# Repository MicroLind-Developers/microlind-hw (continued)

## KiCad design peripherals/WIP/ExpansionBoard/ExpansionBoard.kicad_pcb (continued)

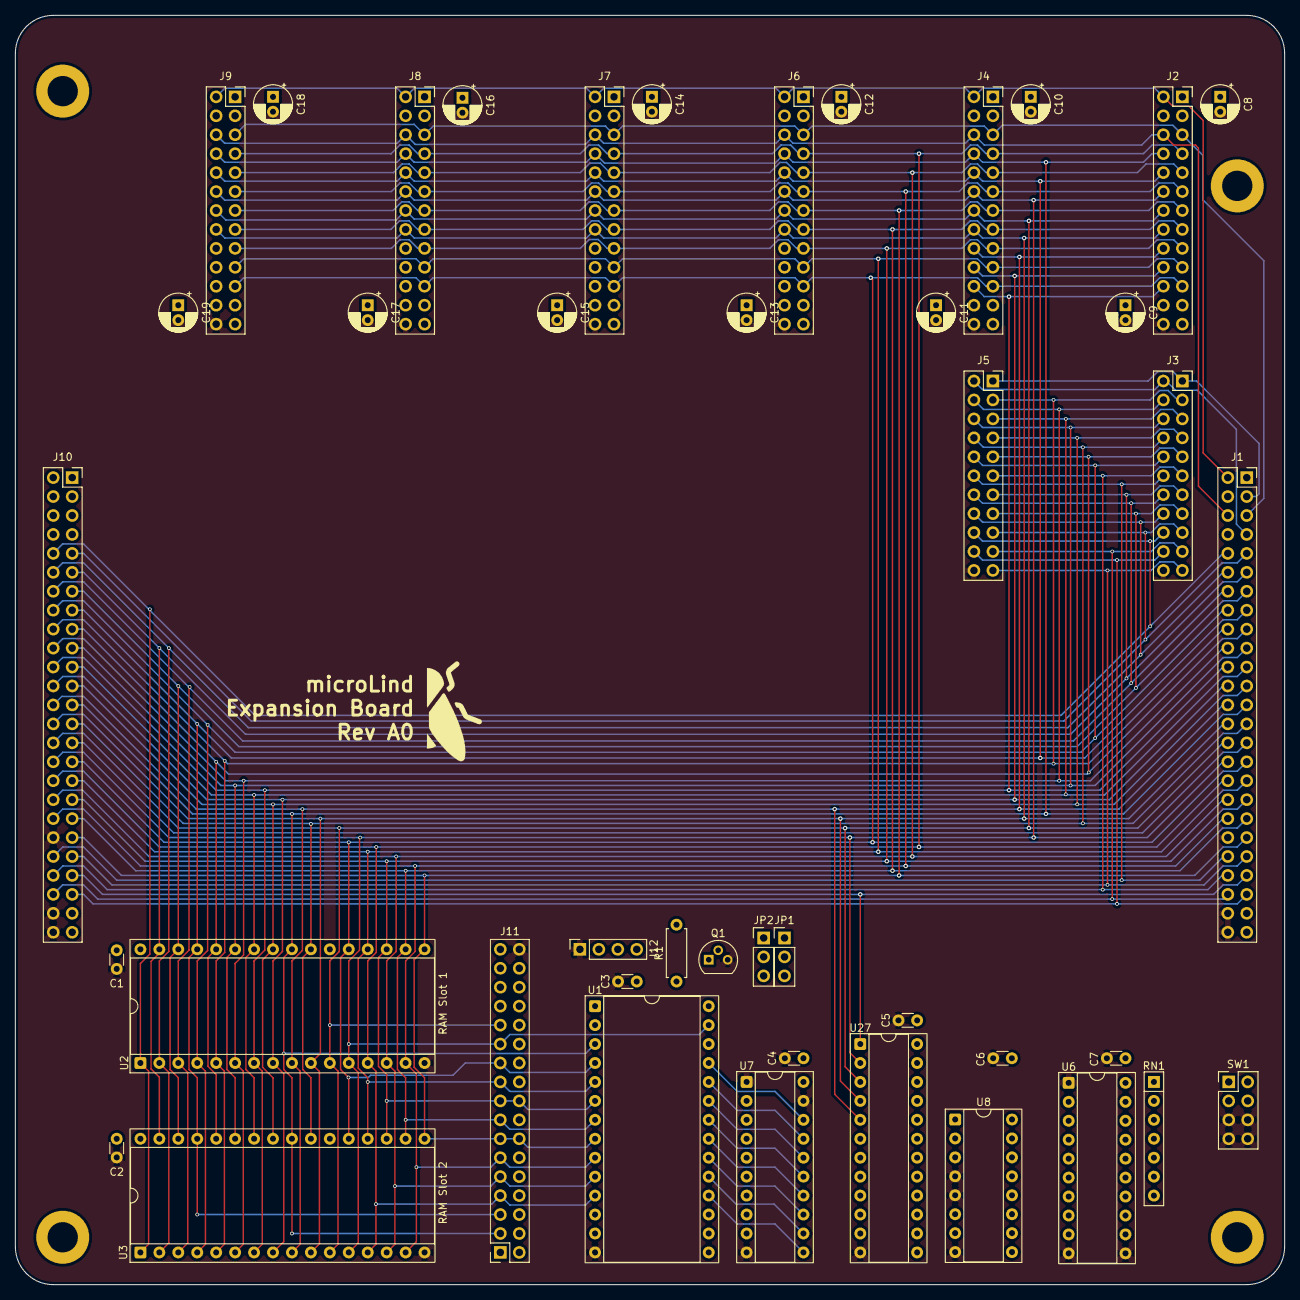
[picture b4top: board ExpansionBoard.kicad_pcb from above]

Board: 4 copper layers, 170.2 x 170.2 mm, 45 parts (0 on the bottom side), 94 nets.

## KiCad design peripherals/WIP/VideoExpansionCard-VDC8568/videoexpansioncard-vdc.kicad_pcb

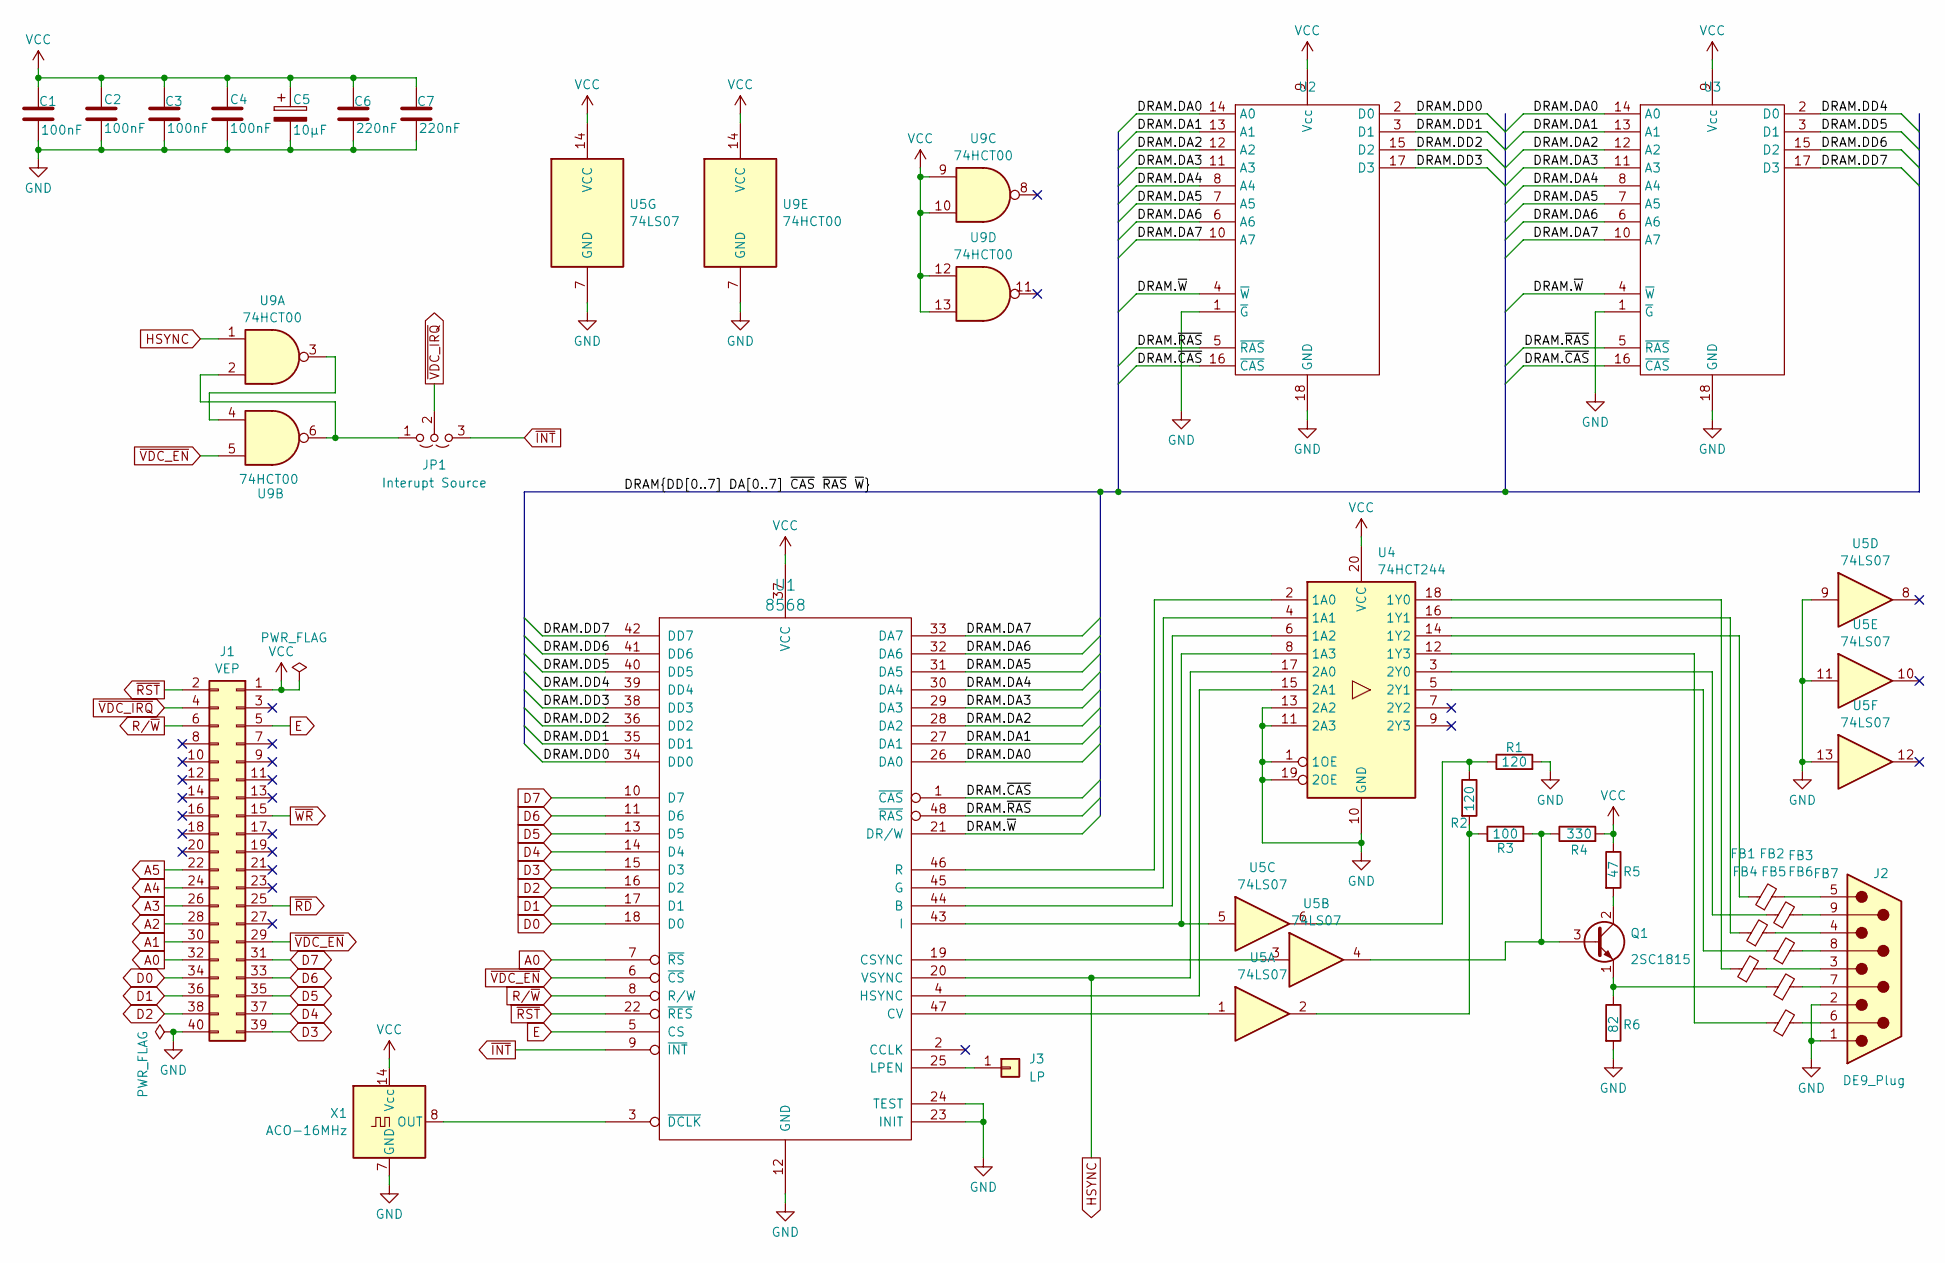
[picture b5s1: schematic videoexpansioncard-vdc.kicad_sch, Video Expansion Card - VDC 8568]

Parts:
C1, C2, C3, C4: 100nF; C_Disc_D5.0mm_W2.5mm_P2.50mm
C5: 10µF; CP_Radial_D5.0mm_P2.00mm
C6, C7: 220nF; C_Disc_D5.0mm_W2.5mm_P2.50mm
FB1, FB2, FB3, FB4, FB5, FB6, FB7: FerriteBead_Small; L_Axial_L5.0mm_D3.6mm_P10.00mm_Horizontal_Murata_BL01RN1A2A2
J1: VEP; GraphicsCardTemplate
J2: DE9_Plug; DSUB-9_Male_Horizontal_P2.77x2.54mm_EdgePinOffset9.40mm
J3: LP; PinHeader_1x01_P2.54mm_Vertical
JP1: Interupt Source; PinHeader_1x03_P2.54mm_Vertical
Q1: 2SC1815; TO-92_Inline
R1, R2: 120; R_Axial_DIN0207_L6.3mm_D2.5mm_P10.16mm_Horizontal
R3: 100; R_Axial_DIN0207_L6.3mm_D2.5mm_P10.16mm_Horizontal
R4: 330; R_Axial_DIN0207_L6.3mm_D2.5mm_P10.16mm_Horizontal
R5: 47; R_Axial_DIN0207_L6.3mm_D2.5mm_P10.16mm_Horizontal
R6: 82; R_Axial_DIN0207_L6.3mm_D2.5mm_P10.16mm_Horizontal
U1: 8568; DIP-48_W15.24mm_Socket
U2, U3: DIP-18_W7.62mm_Socket
U4: 74HCT244; DIP-20_W7.62mm_Socket
U5: 74LS07; DIP-14_W7.62mm_Socket
U9: 74HCT00; DIP-14_W7.62mm_Socket
X1: ACO-16MHz; Oscillator_DIP-14

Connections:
/DRAM.DA0: U1.26 (DA0), U2.14 (A0), U3.14 (A0)
/DRAM.DA1: U1.27 (DA1), U2.13 (A1), U3.13 (A1)
/DRAM.DA2: U1.28 (DA2), U2.12 (A2), U3.12 (A2)
/DRAM.DA3: U1.29 (DA3), U2.11 (A3), U3.11 (A3)
/DRAM.DA4: U1.30 (DA4), U2.8 (A4), U3.8 (A4)
/DRAM.DA5: U1.31 (DA5), U2.7 (A5), U3.7 (A5)
/DRAM.DA6: U1.32 (DA6), U2.6 (A6), U3.6 (A6)
/DRAM.DA7: U1.33 (DA7), U2.10 (A7), U3.10 (A7)
/DRAM.DD0: U1.34 (DD0), U2.2 (D0)
/DRAM.DD1: U1.35 (DD1), U2.3 (D1)
/DRAM.DD2: U1.36 (DD2), U2.15 (D2)
/DRAM.DD3: U1.38 (DD3), U2.17 (D3)
/DRAM.DD4: U1.39 (DD4), U3.2 (D0)
/DRAM.DD5: U1.40 (DD5), U3.3 (D1)
/DRAM.DD6: U1.41 (DD6), U3.15 (D2)
/DRAM.DD7: U1.42 (DD7), U3.17 (D3)
/DRAM.~CAS: U1.1 (~CAS), U2.16 (~CAS), U3.16 (~CAS)
/DRAM.~RAS: U1.48 (~RAS), U2.5 (~RAS), U3.5 (~RAS)
/DRAM.~W: U1.21 (DR/W), U2.4 (~W), U3.4 (~W)
A0: J1.32, U1.7 (~RS)
A1: J1.30
A2: J1.28
A3: J1.26
A4: J1.24
A5: J1.22
D0: J1.34, U1.18 (D0)
D1: J1.36, U1.17 (D1)
D2: J1.38, U1.16 (D2)
D3: J1.39, U1.15 (D3)
D4: J1.37, U1.14 (D4)
D5: J1.35, U1.13 (D5)
D6: J1.33, U1.11 (D6)
D7: J1.31, U1.10 (D7)
E: J1.5, U1.5 (CS)
GND: C1.2, C2.2, C3.2, C4.2, C5.2, C6.2, C7.2, J1.40, J2.1, J2.2, R1.2, R6.2, U1.12 (GND), U1.23 (INIT), U1.24 (TEST), U2.1 (~G), U2.18 (GND), U3.1 (~G), U3.18 (GND), U4.1 (1OE), U4.10 (GND), U4.11 (2A3), U4.13 (2A2), U4.19 (2OE), U5.7 (GND), U5.9, U5.11, U5.13, U9.7 (GND), X1.7 (GND)
HSYNC: U1.20 (VSYNC), U4.17 (2A0), U9.1
unnamed: FB1.2, J2.5
unnamed: FB2.2, J2.9
unnamed: FB3.2, J2.4
unnamed: FB4.2, J2.8
unnamed: FB5.2, J2.3
unnamed: FB6.2, J2.7
unnamed: FB7.2, J2.6
unnamed: J3.1 (Pin_1_1), U1.25 (LPEN)
unnamed: JP1.1 (A), U9.2, U9.6
unnamed: Q1.3 (B), R3.2, R4.1, U5.4
unnamed: Q1.2 (C), R5.2
unnamed: FB6.1, Q1.1 (E), R6.1
unnamed: R1.1, R2.1, U5.6
unnamed: R2.2, R3.1, U5.2
unnamed: U1.44 (B), U4.6 (1A2)
unnamed: U1.19 (CSYNC), U5.3
unnamed: U1.47 (CV), U5.1
unnamed: U1.45 (G), U4.4 (1A1)
unnamed: U1.4 (HSYNC), U4.15 (2A1)
unnamed: U1.43 (I), U4.8 (1A3), U5.5
unnamed: U1.46 (R), U4.2 (1A0)
unnamed: U1.3 (~DCLK), X1.8 (OUT)
unnamed: FB5.1, U4.18 (1Y0)
unnamed: FB3.1, U4.16 (1Y1)
unnamed: FB1.1, U4.14 (1Y2)
unnamed: FB7.1, U4.12 (1Y3)
unnamed: FB2.1, U4.3 (2Y0)
unnamed: FB4.1, U4.5 (2Y1)
unnamed: U9.3, U9.4
R/~W: J1.6, U1.8 (R/W)
VCC: C1.1, C2.1, C3.1, C4.1, C5.1, C6.1, C7.1, J1.1, R4.2, R5.1, U1.37 (VCC), U2.9 (Vcc), U3.9 (Vcc), U4.20 (VCC), U5.14 (VCC), U9.9, U9.10, U9.12, U9.13, U9.14 (VCC), X1.14 (Vcc)
~INT: JP1.3 (B), U1.9 (~INT)
~RD: J1.25
~RST: J1.2, U1.22 (~RES)
~VDC_EN: J1.29, U1.6 (~CS), U9.5
~VDC_IRQ: J1.4, JP1.2 (C)
~WR: J1.15

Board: 2 copper layers, 32 parts (0 on the bottom side), 66 nets, no tracks yet.

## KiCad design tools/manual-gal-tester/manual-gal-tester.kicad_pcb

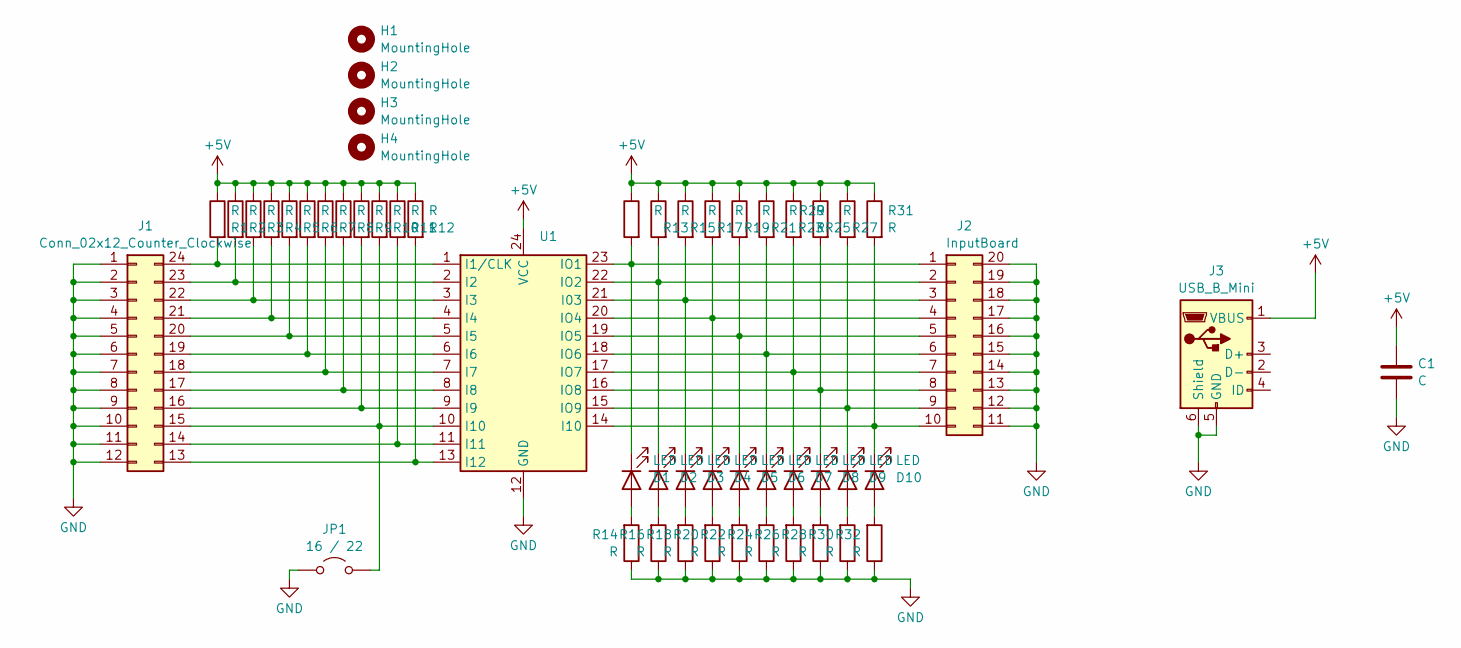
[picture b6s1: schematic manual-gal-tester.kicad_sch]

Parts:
C1: C; C_Radial_D5.0mm_H5.0mm_P2.00mm
D1, D2, D3, D4, D5, D6, D7, D8, D9, D10: LED; LED_D5.0mm
H1, H2, H3, H4: MountingHole; MountingHole_3.2mm_M3
J1: Conn_02x12_Counter_Clockwise; DIP-24_W7.62mm_Socket
J2: InputBoard; DIP-20_W7.62mm_Socket
J3: USB_B_Mini; USB_B_Lumberg_2411_02_Horizontal
JP1: 16 / 22; PinHeader_1x02_P2.54mm_Vertical
R1, R2, R3, R4, R5, R6, R7, R8, R9, R10, R11, R12, R13, R14, R15, R16, R17, R18, R19, R20, R21, R22, R23, R24, R25, R26, R27, R28, R29, R30, R31, R32: R; R_Axial_DIN0207_L6.3mm_D2.5mm_P2.54mm_Vertical
U1: DIP_Socket-24_W4.3_W5.08_W7.62_W10.16_W10.9_3M_224-5248-00-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

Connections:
+5V: C1.1, J3.1 (VBUS), R1.1, R2.1, R3.1, R4.1, R5.1, R6.1, R7.1, R8.1, R9.1, R10.1, R11.1, R12.1, R13.1, R15.1, R17.1, R19.1, R21.1, R23.1, R25.1, R27.1, R29.1, R31.1, U1.24 (VCC)
GND: C1.2, J1.1, J1.2, J1.3, J1.4, J1.5, J1.6, J1.7, J1.8, J1.9, J1.10, J1.11, J1.12, J2.11, J2.12, J2.13, J2.14, J2.15, J2.16, J2.17, J2.18, J2.19, J2.20, J3.5 (GND), J3.6 (Shield), JP1.1 (A), R14.1, R16.1, R18.1, R20.1, R22.1, R24.1, R26.1, R28.1, R30.1, R32.1, U1.12 (GND)
unnamed: D1.2 (A), R14.2
unnamed: D1.1 (K), J2.1, R13.2, U1.23 (IO1)
unnamed: D2.2 (A), R16.2
unnamed: D2.1 (K), J2.2, R15.2, U1.22 (IO2)
unnamed: D3.2 (A), R18.2
unnamed: D3.1 (K), J2.3, R17.2, U1.21 (I03)
unnamed: D4.2 (A), R20.2
unnamed: D4.1 (K), J2.4, R19.2, U1.20 (IO4)
unnamed: D5.2 (A), R22.2
unnamed: D5.1 (K), J2.5, R21.2, U1.19 (IO5)
unnamed: D6.2 (A), R24.2
unnamed: D6.1 (K), J2.6, R23.2, U1.18 (IO6)
unnamed: D7.2 (A), R26.2
unnamed: D7.1 (K), J2.7, R25.2, U1.17 (IO7)
unnamed: D8.2 (A), R28.2
unnamed: D8.1 (K), J2.8, R27.2, U1.16 (IO8)
unnamed: D9.2 (A), R30.2
unnamed: D9.1 (K), J2.9, R29.2, U1.15 (IO9)
unnamed: D10.2 (A), R32.2
unnamed: D10.1 (K), J2.10, R31.2, U1.14 (I10)
unnamed: J1.13, R12.2, U1.13 (I12)
unnamed: J1.14, R11.2, U1.11 (I11)
unnamed: J1.15, JP1.2 (B), R10.2, U1.10 (I10)
unnamed: J1.16, R9.2, U1.9 (I9)
unnamed: J1.17, R8.2, U1.8 (I8)
unnamed: J1.18, R7.2, U1.7 (I7)
unnamed: J1.19, R6.2, U1.6 (I6)
unnamed: J1.20, R5.2, U1.5 (I5)
unnamed: J1.21, R4.2, U1.4 (I4)
unnamed: J1.22, R3.2, U1.3 (I3)
unnamed: J1.23, R2.2, U1.2 (I2)
unnamed: J1.24, R1.2, U1.1 (I1/CLK)

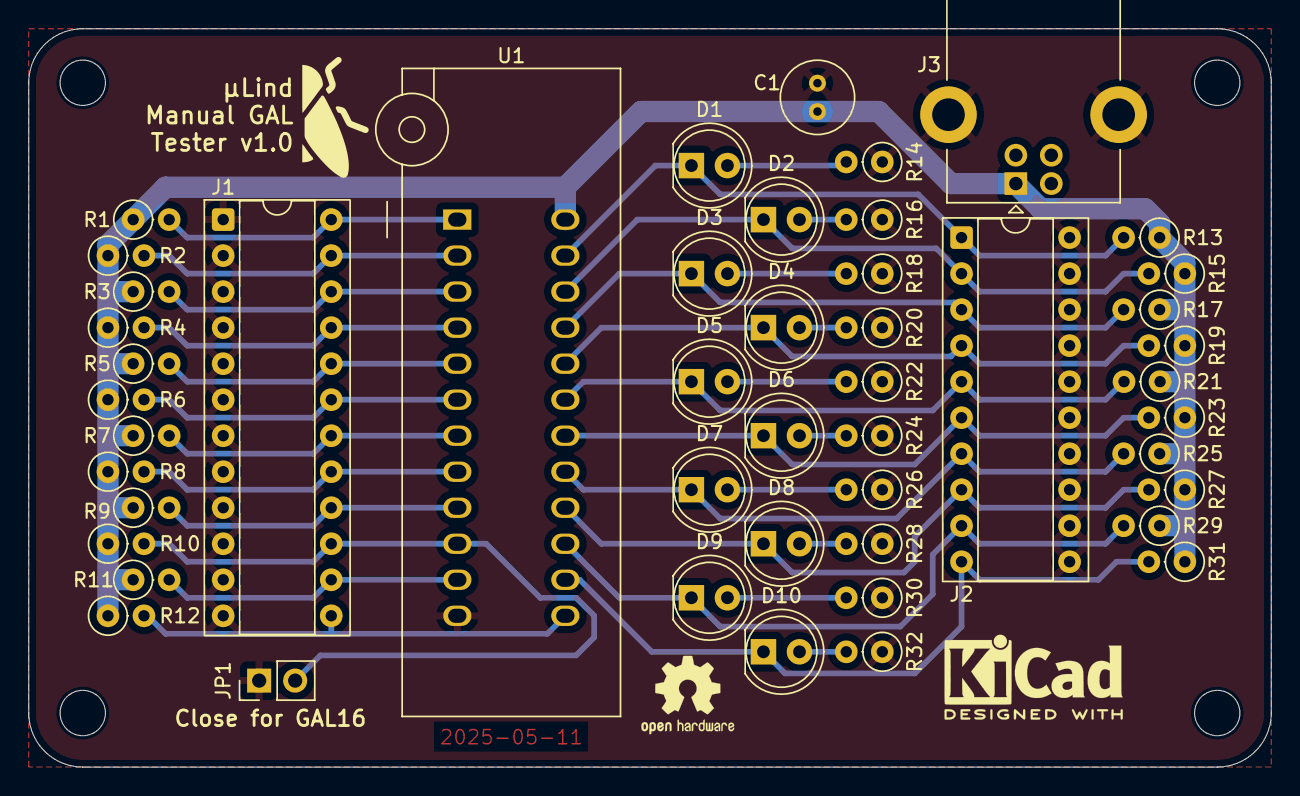
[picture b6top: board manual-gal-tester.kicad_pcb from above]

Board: 2 copper layers, 87.6 x 52.1 mm, 52 parts (0 on the bottom side), 34 nets.

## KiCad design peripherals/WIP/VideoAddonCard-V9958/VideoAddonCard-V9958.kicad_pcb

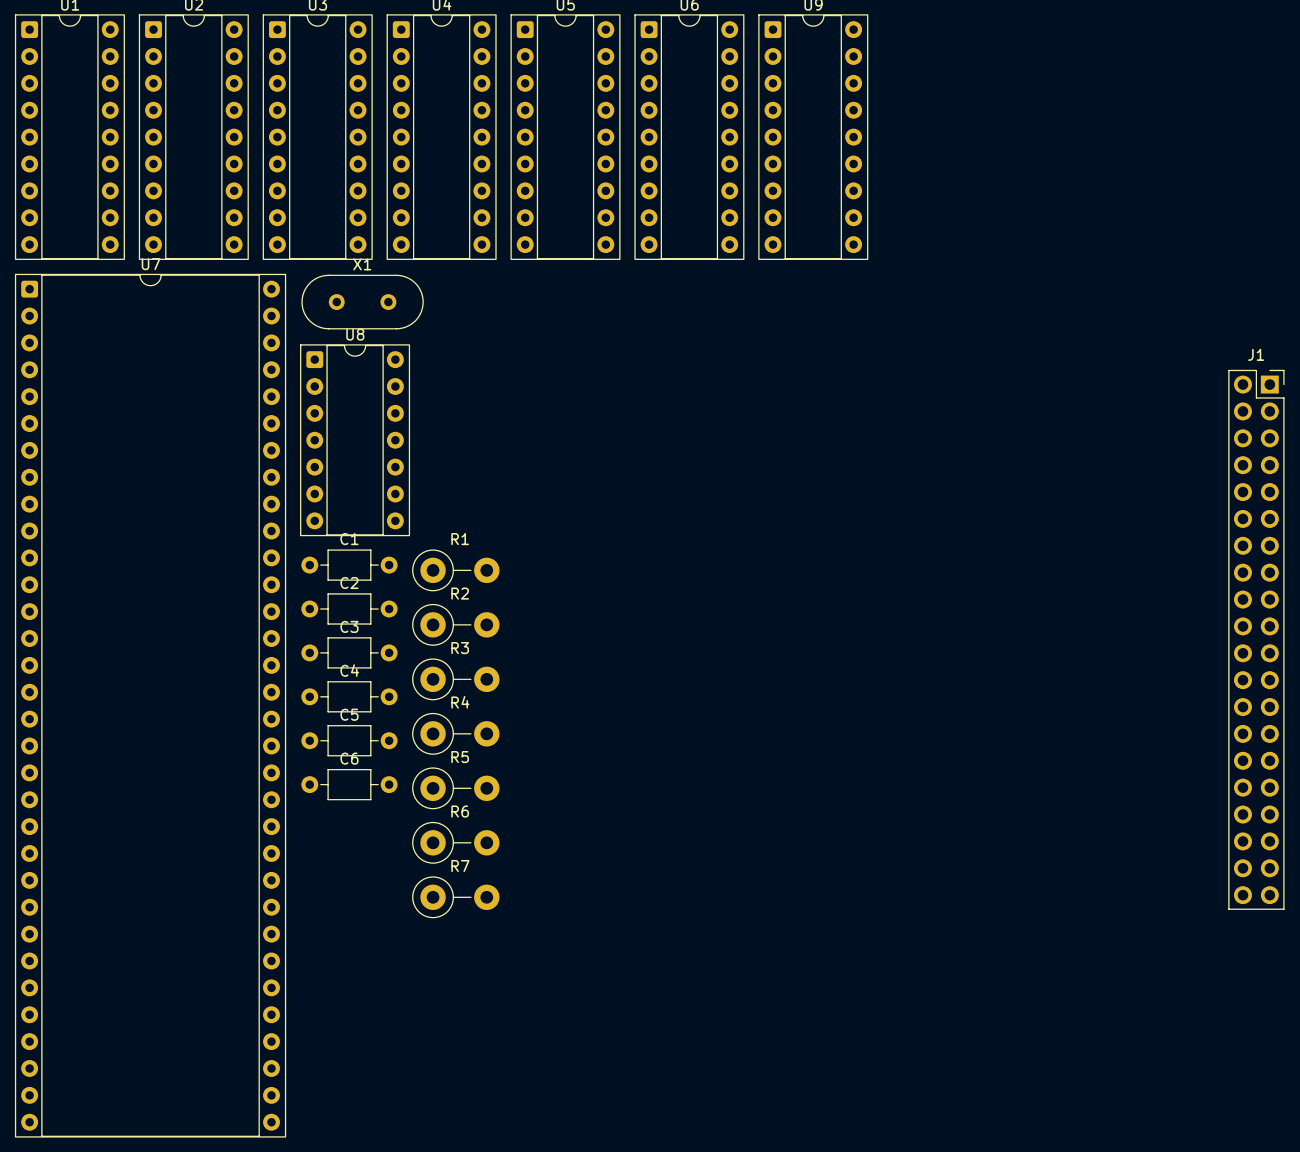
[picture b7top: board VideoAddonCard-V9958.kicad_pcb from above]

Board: 2 copper layers, 24 parts (0 on the bottom side), 53 nets, no tracks yet.

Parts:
C1, C2: C; C_Axial_L3.8mm_D2.6mm_P7.50mm_Horizontal
C3, C4, C5: 100nF; C_Axial_L3.8mm_D2.6mm_P7.50mm_Horizontal
C6: 47pF; C_Axial_L3.8mm_D2.6mm_P7.50mm_Horizontal
J1: VideoAddon; PinSocket_2x20_P2.54mm_Vertical
R1, R2, R3: 470; R_Axial_DIN0411_L9.9mm_D3.6mm_P5.08mm_Vertical
R4: 2k61; R_Axial_DIN0411_L9.9mm_D3.6mm_P5.08mm_Vertical
R5, R6: 4k7; R_Axial_DIN0411_L9.9mm_D3.6mm_P5.08mm_Vertical
R7: 2k2; R_Axial_DIN0411_L9.9mm_D3.6mm_P5.08mm_Vertical
U1, U2, U3, U4, U5, U6: 41464; DIP-18_W7.62mm_Socket
U7: V9958; DIP-64_W22.86mm_Socket
U8: 74LS32; DIP-14_W7.62mm_Socket
U9: DIP-18_W7.62mm_Socket
X1: Crystal_Generic; Crystal_HC49-4H_Vertical

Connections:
/A0: J1.32, U7.29 (A0)
/A1: J1.30, U7.28 (A1)
B_OUT: C5.1, R3.1, U7.24 (BLUE)
D0: J1.34, U7.40 (D0)
D1: J1.36, U7.39 (D1)
D2: J1.38, U7.38 (D2)
D3: J1.39, U7.37 (D3)
D4: J1.37, U7.36 (D4)
D5: J1.35, U7.35 (D5)
D6: J1.33, U7.34 (D6)
D7: J1.31, U7.32 (D7)
GND: C1.1, C2.1, C6.1, J1.40, R1.2, R2.2, R3.2, U1.18 (GND), U2.18 (GND), U3.18 (GND), U4.18 (GND), U5.18 (GND), U6.18 (GND), U7.1 (GND), U7.20 (GND/DAC), U8.9, U8.10, U8.12, U8.13, U9.1 (GND), U9.7 (N_PIN)
G_OUT: C4.1, R1.1, U7.23 (RED)
unnamed: C3.2, U9.2 (B_IN)
unnamed: C5.2, U9.4 (B_IN)
unnamed: C1.2, U7.63 (XTAL1), X1.1
unnamed: C2.2, U7.64 (XTAL2), X1.2
unnamed: U7.31 (~CSR), U8.6
unnamed: U7.30 (~CSW), U8.3
unnamed: R5.1, U7.27 (~H_RESET)
unnamed: R6.1, U7.4 (~V_RESET)
unnamed: C4.2, U9.3 (G_IN)
unnamed: C6.2, R7.2, U9.10 (SYNC_IN)
unnamed: R4.2, U9.17 (Y_TRAP)
R_OUT: C3.1, R2.1, U7.22 (GREEN)
VA0: U1.14 (A0), U2.14 (A0), U3.14 (A0), U4.14 (A0), U5.14 (A0), U6.14 (A0), U7.49 (VA0)
VA1: U1.13 (A1), U2.13 (A1), U3.13 (A1), U4.13 (A1), U5.13 (A1), U6.13 (A1), U7.50 (VA1)
VA2: U1.12 (A2), U2.12 (A2), U3.12 (A2), U4.12 (A2), U5.12 (A2), U6.12 (A2), U7.51 (VA2)
VA3: U1.11 (A3), U2.11 (A3), U3.11 (A3), U4.11 (A3), U5.11 (A3), U6.11 (A3), U7.52 (VA3)
VA4: U1.8 (A4), U2.8 (A4), U3.8 (A4), U4.8 (A4), U5.8 (A4), U6.8 (A4), U7.53 (VA4)
VA5: U1.7 (A5), U2.7 (A5), U3.7 (A5), U4.7 (A5), U5.7 (A5), U6.7 (A5), U7.54 (VA5)
VA6: U1.6 (A6), U2.6 (A6), U3.6 (A6), U4.6 (A6), U5.6 (A6), U6.6 (A6), U7.55 (VA6)
VA7: U1.10 (A7), U2.10 (A7), U3.10 (A7), U4.10 (A7), U5.10 (A7), U6.10 (A7), U7.56 (VA7)
VCC: J1.1, R4.1, R5.2, R6.2, U1.9 (VCC), U2.9 (VCC), U3.9 (VCC), U4.9 (VCC), U5.9 (VCC), U6.9 (VCC), U7.21 (VCC/DAC), U7.58 (VCC), U9.12 (VCC)
VD0: U1.2 (D0), U3.2 (D0), U5.2 (D0), U7.41 (VD0)
VD1: U1.3 (D1), U3.3 (D1), U5.3 (D1), U7.42 (VD1)
VD2: U1.15 (D2), U3.15 (D2), U5.15 (D2), U7.43 (VD2)
VD3: U1.17 (D3), U3.17 (D3), U5.17 (D3), U7.44 (VD3)
VD4: U2.2 (D0), U4.2 (D0), U6.2 (D0), U7.45 (VD4)
VD5: U2.3 (D1), U4.3 (D1), U6.3 (D1), U7.46 (VD5)
VD6: U2.15 (D2), U4.15 (D2), U6.15 (D2), U7.47 (VD6)
VD7: U2.17 (D3), U4.17 (D3), U6.17 (D3), U7.48 (VD7)
_CAS0: U1.16 (~CAS), U2.16 (~CAS), U7.61 (~CAS0)
_CAS1: U3.16 (~CAS), U4.16 (~CAS), U7.60 (~CAS1)
_CAS2: U5.16 (~CAS), U6.16 (~CAS), U7.59 (~CASX)
_R: U1.1 (~OE), U2.1 (~OE), U3.1 (~OE), U4.1 (~OE), U5.1 (~OE), U6.1 (~OE)
_RAS: U1.5 (~RAS), U2.5 (~RAS), U3.5 (~RAS), U4.5 (~RAS), U5.5 (~RAS), U6.5 (~RAS), U7.62 (~RAS)
_W: U1.4 (~W), U2.4 (~W), U3.4 (~W), U4.4 (~W), U5.4 (~W), U6.4 (~W)
~IRQ: J1.4, U7.25 (~INT)
~RD: J1.25, U8.5
~RST: J1.2, U7.9 (~RESET)
~VDC_EN: J1.29, U8.1, U8.4
~WR: J1.15, U8.2

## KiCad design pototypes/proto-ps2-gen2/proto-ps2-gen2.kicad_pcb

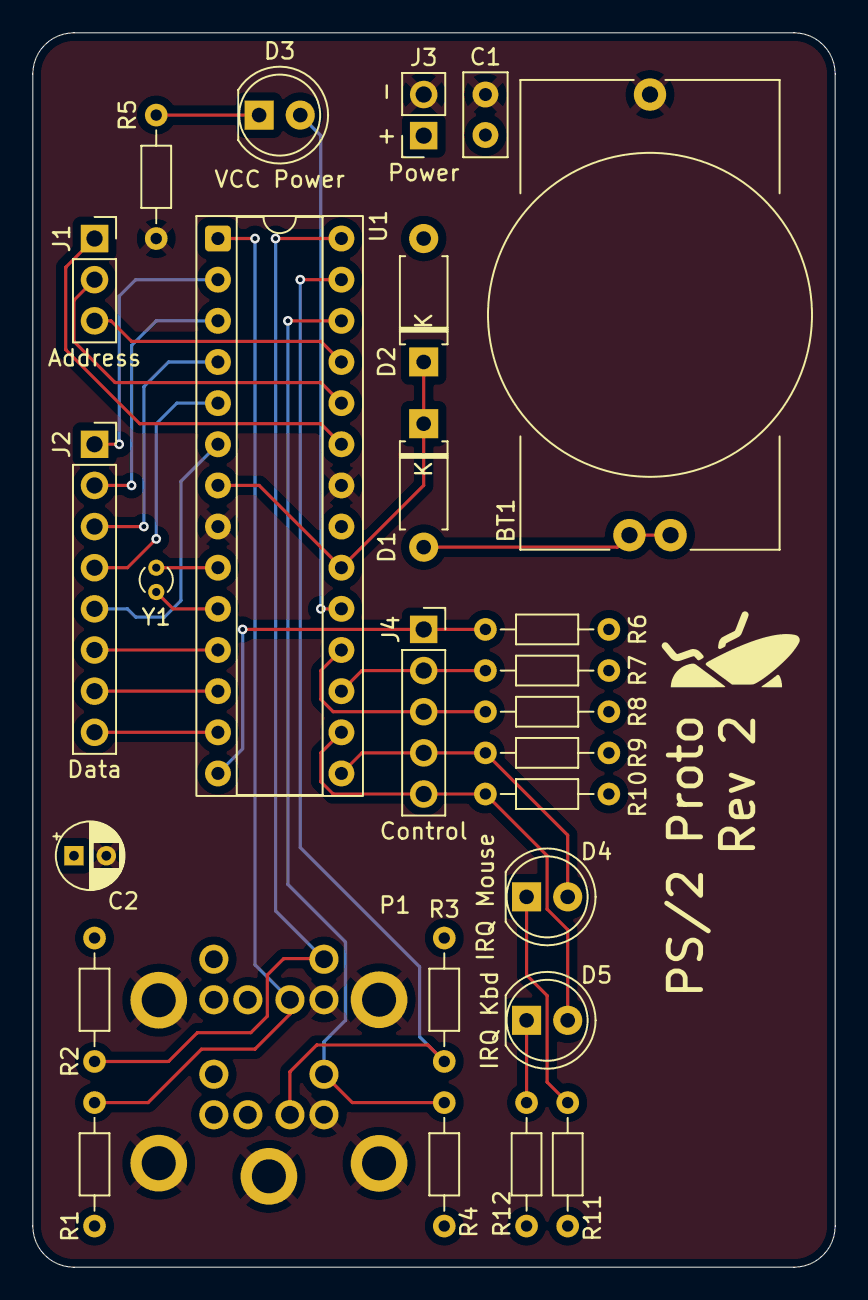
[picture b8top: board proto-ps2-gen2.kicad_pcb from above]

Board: 2 copper layers, 49.5 x 76.2 mm, 27 parts (0 on the bottom side), 30 nets.

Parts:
BT1: 2032; HU2032-CoinCellHolder
C1: 100n; C_Disc_D5.0mm_W2.5mm_P2.50mm
C2: 10u; CP_Radial_D4.0mm_P2.00mm
D1, D2: BAT41; D_A-405_P7.62mm_Horizontal
D3: VCC Power; LED_D5.0mm
D4: IRQ Mouse; LED_D5.0mm
D5: IRQ Kbd; LED_D5.0mm
J1: Address; PinSocket_1x03_P2.54mm_Vertical
J2: Data; PinSocket_1x08_P2.54mm_Vertical
J3: Power; PinSocket_1x02_P2.54mm_Vertical
J4: Control; PinSocket_1x05_P2.54mm_Vertical
P1: 2xPS2-Mini-Din
R1, R2, R3, R4, R6, R7, R8, R9, R10: 10k; R_Axial_DIN0204_L3.6mm_D1.6mm_P7.62mm_Horizontal
R5, R11, R12: 470; R_Axial_DIN0204_L3.6mm_D1.6mm_P7.62mm_Horizontal
U1: ATmega88; DIP-28_W7.62mm_Socket
Y1: 32.768kHz; Crystal_DS10_D1.0mm_L4.3mm_Vertical

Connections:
/A0: J1.1, U1.23 (PC0)
/A1: J1.2, U1.24 (PC1)
/A2: J1.3, U1.25 (PC2)
/D0: J2.1, U1.2 (PD0)
/D1: J2.2, U1.3 (PD1)
/D2: J2.3, U1.4 (PD2)
/D3: J2.4, U1.5 (PD3)
/D4: J2.5, U1.6 (PD4)
/D5: J2.6, U1.11 (PD5)
/D6: J2.7, U1.12 (PD6)
/D7: J2.8, U1.13 (PD7)
/PS2_KB_CLK: P1.11 (Kbd_Clock), R4.1, U1.26 (PC3)
/PS2_KB_DATA: P1.7 (Kbd_Data), R3.1, U1.27 (PC4)
/PS2_M_CLK: P1.5 (Mouse_Clock), R2.1, U1.28 (PC5)
/PS2_M_DATA: P1.1 (Mouse_Data), R1.1, U1.1 (~RESET/PC6)
/~INT_PS2_KB: D5.2 (A), J4.5, R10.1, U1.16 (PB2)
/~INT_PS2_M: D4.2 (A), J4.4, R9.1, U1.15 (PB1)
/~PS2_EN: J4.1, R6.1, U1.14 (PB0)
/~RD: J4.2, R7.1, U1.17 (PB3)
/~WR: J4.3, R8.1, U1.18 (PB4)
GND: BT1.2 (-), C1.2, C2.2, J3.2, P1.3 (Mouse_GND), P1.9 (Kbd_GND), P1.G (GND), R5.1, U1.8 (GND), U1.22 (GND)
unnamed: BT1.1 (+), D1.2 (A)
unnamed: D1.1 (K), D2.1 (K), U1.7 (VCC), U1.20 (AVCC)
unnamed: D3.2 (A), U1.19 (PB5)
unnamed: D3.1 (K), R5.2
unnamed: D4.1 (K), R11.2
unnamed: D5.1 (K), R12.2
unnamed: U1.9 (XTAL1/PB6), Y1.1
unnamed: U1.10 (XTAL2/PB7), Y1.2
VCC: C1.1, C2.1, D2.2 (A), J3.1, P1.4 (Mouse_PWR), P1.10 (Kbd_PWR), R1.2, R2.2, R3.2, R4.2, R6.2, R7.2, R8.2, R9.2, R10.2, R11.1, R12.1

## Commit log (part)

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2024-07-31 Initial commit of splitted hardware repo for µLind
2024-10-16 Added stage2 to prototypes
2024-10-16 Added 6522 proto board
2024-10-16 Several proto boards for stage 1 board
2024-10-16 Moved OPL to correct location. Added Expansion bord and card template.
2024-10-16 Eh...
2024-10-17 MMU read capability added
2024-10-17 in between commits
2024-10-17 Started layout of board with mmu read register
2024-10-19 Finalized stage 2
2024-10-28 Manual merge
    Merging all branches manually after realizing that version handling hardware using branches was a terrible idea.
2024-10-30 Major restructure of hw repository
    And added step, schematic, gerber and a picture
2024-11-15 Updates to peripherials and stage2 & 3
2024-11-17 Ordered stage 2!
2025-04-01 Updated stage 2 and stage 3, and started on a cf addon
2025-04-23 Updated dru file for PCBWay
2025-04-23 Added expansion layout
2025-04-24 Started on the expansion base
2025-04-24 Updates to a lot!
2025-04-25 Started on the expansion backplane
2025-04-27 Updates to Expansion
2025-05-23 Added a manual tester board for gals
2025-07-31 Updated stage 3
2025-08-05 Updated stage 3 with ps2 fix, added warning to PS/2 proto
2025-08-05 Added license notification
2025-08-05 Fixed logos
2025-08-28 Added new ps handling in stage3-rev1
2025-10-29 A lot of updates
2025-11-05 Updatesto Expansion
2025-11-06 Started on IDE interface card and a multi-serial (UART, I2C and SPI) card
2026-01-04 Before adding 3-8 decoder for more enable signals.
2026-01-07 Added Support for protected mode, routed R/W thru logic to amplify.
